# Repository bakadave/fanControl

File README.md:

# fanControl readme

## EEPROM memory map

| memory location | data type | Description|
| ----------- | ----------- | ----------- |
| 1 | bool | WiFi on |
| 2 | bool | 5V PSU |
| 3 | bool | USB sense |
| 4 | float | cal_a |
| 5 |  | cal_a |
| 6 |  | cal_a |
| 7 |  | cal_a |
| 8 | float | cal_b |
| 9 |  | cal_b |
| 10 | | cal_b |
| 11 | | cal_b |
| 12 | char[16] | hostname |
| 13 | | hostname |
| 14 | | hostname |
| 15 | | hostname |
| 16 | | hostname |
| 17 | | hostname |
| 18 | | hostname |
| 19 | | hostname |
| 20 | | hostname |
| 21 | | hostname |
| 22 | | hostname |
| 23 | | hostname |
| 24 | | hostname |
| 25 | | hostname |
| 26 | | hostname |
| 27 | | hostname |
| 28 | N/A | unused |
| 29 | N/A | unused |
| 30 | N/A | unused |
| 31 | N/A | unused |
| 32 | N/A | unused |

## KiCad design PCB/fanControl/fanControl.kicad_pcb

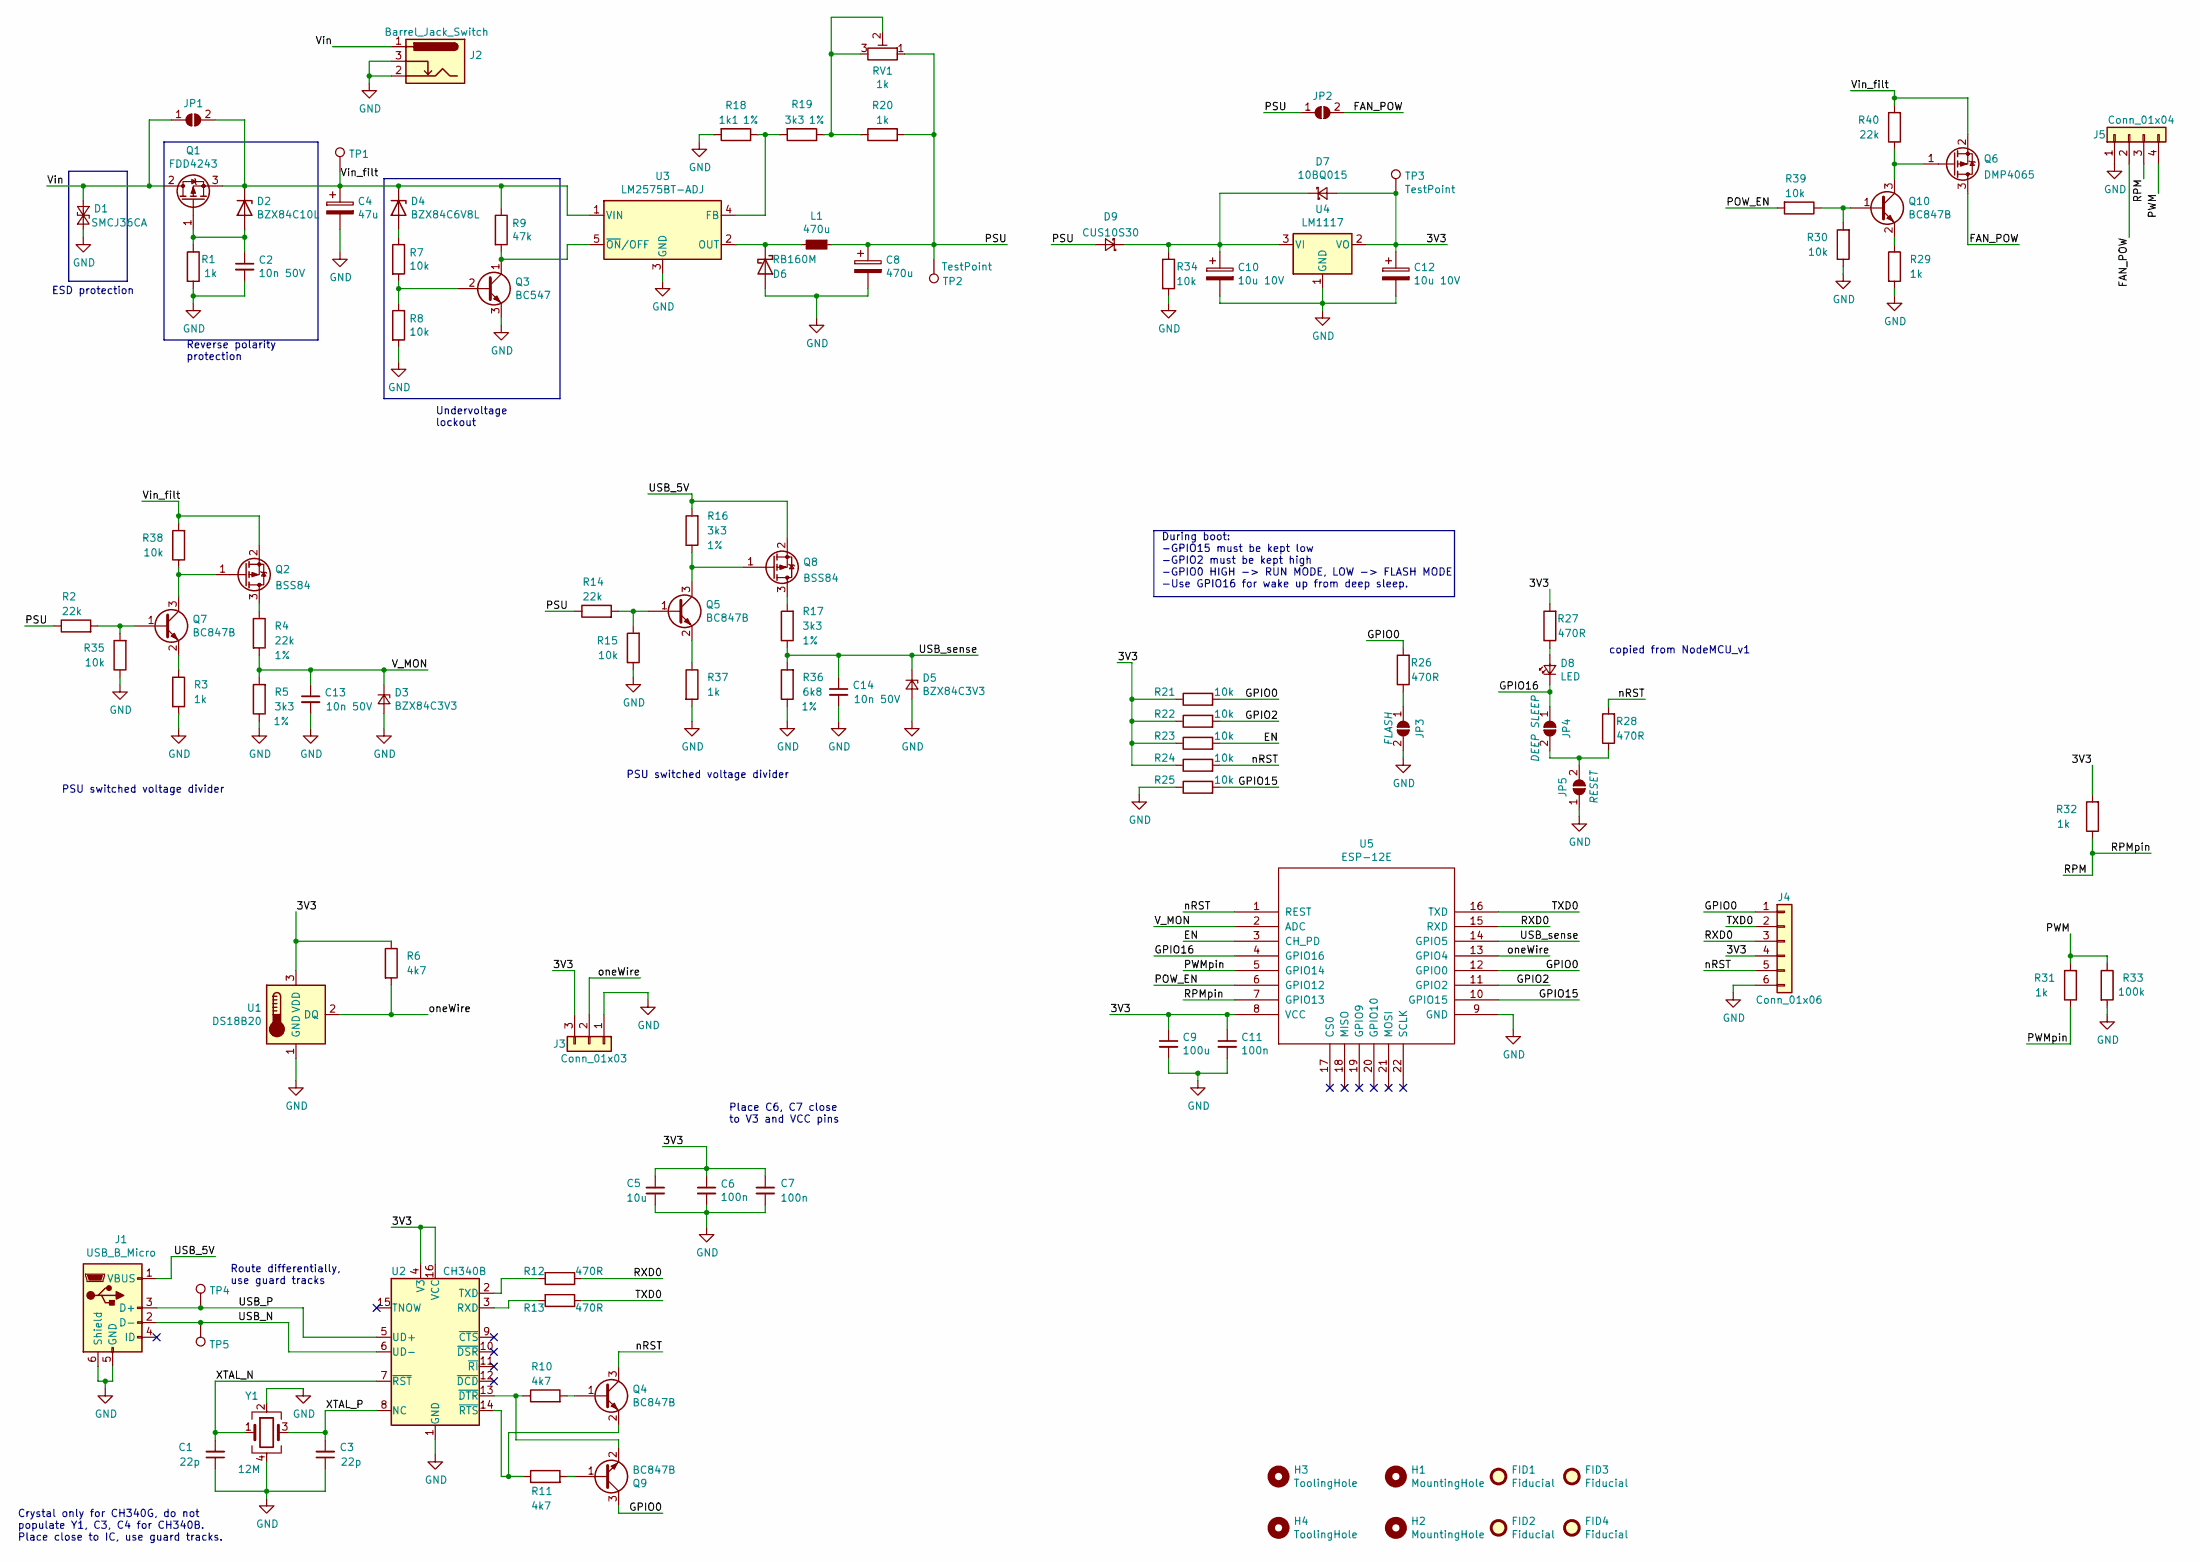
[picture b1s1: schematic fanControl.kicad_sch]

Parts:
C1, C3: 22p; CAP_0805; MPN CC0805FRNPO9BN220; LCSC C541515
C2, C13, C14: 10n 50V; CAP_0805; MPN CC0805JKNPO9BN103; LCSC C527201
C4: 47u; C_Radial_D6.3mm_H11.0mm_P2.50mm
C5: 10u; CAP_0805; MPN CC0805ZKY5V6BB106; LCSC C88484
C6, C7, C11: 100n; CAP_0805; MPN CC0805KRX7R9BB104; LCSC C49678
C8: 470u; C_Radial_D8.0mm_H11.5mm_P3.50mm
C9: 100u; C_1206_3216Metric; MPN CC1206MKX5R5BB107; LCSC C110048
C10, C12: 10u 10V; CP_EIA-3216-18_Kemet-A_Pad1.58x1.35mm_HandSolder; MPN T529P106M010AAE200; LCSC C696821
D1: SMCJ36CA; D_SMC; MPN SMCJ36CA; LCSC C2831485
D2: BZX84C10L; D_SOT-23_ANK; MPN BZX84C10LT1G; LCSC C82476
D3, D5: BZX84C3V3; D_SOT-23_ANK; MPN BZX84C3V3LT1G; LCSC C82473
D4: BZX84C6V8L; D_SOT-23_ANK; MPN BZX84C6V8LT1G; LCSC C90848
D6: RB160M; D_SOD-123; MPN RB160M-40TR; LCSC C123003
D7: 10BQ015; D_SMB; MPN VS-10BQ015-M3/5BT; LCSC C413466
D8: LED; LED_0805; MPN 17-215/BHC-AP1Q2/3T; LCSC C131208
D9: CUS10S30; D_SOD-323_HandSoldering; MPN CUS10S30,H3F; LCSC C146335
FID1, FID2, FID3, FID4: Fiducial; Fiducial_0.5mm_Mask1.5mm
H1, H2: MountingHole; MountingHole_3.2mm_M3
H3, H4: ToolingHole; JLC_toolinghole
J1: USB_B_Micro; USB_Micro-B_Molex-105017-0001; MPN 1050170001; LCSC C136000
J2: Barrel_Jack_Switch; BarrelJack_GCT_DCJ200-10-A_Horizontal; MPN 694106301002
J3: Conn_01x03; Molex_KK-254_AE-6410-03A_1x03_P2.54mm_Vertical
J4: Conn_01x06; PinHeader_1x06_P2.54mm_Vertical
J5: Conn_01x04; Molex_KK-254_AE-6410-04A_1x04_P2.54mm_Vertical
JP1, JP2, JP3, JP4, JP5: SolderJumper_2_Open; SolderJumper-2_P1.3mm_Open_TrianglePad1.0x1.5mm
L1: 470u; L_Radial_D10.5mm_P5.00mm_Abacron_AISR-01
Q1: FDD4243; TO-252-2; MPN FDD4243; LCSC C709958
Q2, Q8: BSS84; SOT-23; MPN BSS84PH6327; LCSC C152212
Q3: BC547; TO-92_Inline_Wide; MPN BC547B; LCSC C713613
Q4, Q5, Q7, Q9, Q10: BC847B; SOT-23; MPN BC847BLT1G; LCSC C94393
Q6: DMP4065; SOT-23; MPN DMP4065S-7; LCSC C182476
R1, R3, R20, R29, R31, R32, R37: 1k; RES_0805; MPN RC0805JR-071KL; LCSC C100046
R2, R4, R14, R40: 22k; RES_0805; MPN RC0805FR-0722KL; LCSC C114565
R5, R16, R17, R19: 3k3; RES_0805; MPN RC0805FR-073K3L; LCSC C114531
R6, R10, R11: 4k7; RES_0805; MPN RC0805FR-074K7L; LCSC C60816
R7, R8, R15, R21, R22, R23, R24, R25, R30, R34, R35, R38, R39: 10k; RES_0805; MPN RC0805JR-0710KL; LCSC C100047
R9: 47k; RES_0805; MPN RC0805JR-0747KL; LCSC C131051
R12, R13, R26, R27, R28: 470R; RES_0805; MPN RC0805JR-07470RL; LCSC C114747
R18: 1k1; RES_0805; MPN RC0805FR-071K1L; LCSC C185294
R33: 100k; RES_0805; MPN RC0805JR-07100KL; LCSC C100049
R36: 6k8; RES_0805; MPN RC0805FR-076K8L; LCSC C114550
RV1: 1k; pot; MPN VG039NCHXTB102; LCSC C128543
TP1, TP2, TP3, TP4, TP5: TestPoint; TestPoint_Pad_D1.0mm
U1: DS18B20; TO-92_Inline_Wide; MPN DS18B20+; LCSC C9753
U2: CH340B; SOIC-16_3.9x9.9mm_P1.27mm; MPN CH340B; LCSC C81010
U3: LM2575BT-ADJ; TO-220-5_Vertical; MPN LM2575T-ADJ; LCSC C434579
U4: LM1117; SOT-223-3_TabPin2; MPN LM1117IMPX-3.3/NOPB; LCSC C23984
U5: ESP-12E; MPN ESP-12E; LCSC C89297
Y1: 12M; Crystal_SMD_3225-4Pin_3.2x2.5mm; MPN S3212000101080; LCSC C390763

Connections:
/3V3: C5.1, C6.1, C7.1, C9.1, C11.1, C12.1, D7.2 (A), J3.3, J4.4, R6.1, R21.1, R22.1, R23.1, R24.1, R27.2, R32.2, TP3.1, U1.3 (VDD), U2.4 (V3), U2.16 (VCC), U4.2 (VO), U5.8 (VCC)
/EN: R23.2, U5.3 (CH_PD)
/FAN_POW: J5.2, JP2.2 (B), Q6.3 (D)
/GPIO0: J4.1, Q9.3 (C), R21.2, R26.2, U5.12 (GPIO0)
/GPIO2: R22.2, U5.11 (GPIO2)
/GPIO15: R25.2, U5.10 (GPIO15)
/GPIO16: D8.1 (K), JP4.1 (A), U5.4 (GPIO16)
/POW_EN: R39.2, U5.6 (GPIO12)
/PSU: C8.1, D9.2 (A), JP2.1 (A), L1.1, R2.1, R14.1, R20.2, RV1.1, TP2.1
/PWM: J5.4, R31.2, R33.1
/PWMpin: R31.1, U5.5 (GPIO14)
/RPM: J5.3, R32.1, U5.7 (GPIO13)
/RXD0: J4.3, R12.1, U5.15 (RXD)
/TXD0: J4.2, R13.1, U5.16 (TXD)
/USB_5V: J1.1 (VBUS), Q8.2 (S), R16.2
/USB_N: J1.2 (D-), TP5.1, U2.6 (UD-)
/USB_P: J1.3 (D+), TP4.1, U2.5 (UD+)
/USB_sense: C14.1, D5.1 (K), R17.1, R36.2, U5.14 (GPIO5)
/V_MON: C13.1, D3.1 (K), R4.2, R5.2, U5.2 (ADC)
/Vin: D1.1 (K), J2.1, JP1.1 (A), Q1.2 (D)
/Vin_filt: C4.1, D2.1 (K), D4.1 (K), JP1.2 (B), Q1.3 (S), Q2.2 (S), Q6.2 (S), R9.1, R38.2, R40.2, TP1.1, U3.1 (VIN)
/XTAL_N: C1.2, U2.7 (~RST), Y1.1
/XTAL_P: C3.2, U2.8 (NC), Y1.3
/nRST: J4.5, Q4.3 (C), R24.2, R28.2, U5.1 (REST)
/oneWire: J3.2, R6.2, U1.2 (DQ), U5.13 (GPIO4)
GND: C1.1, C2.2, C3.1, C4.2, C5.2, C6.2, C7.2, C8.2, C9.2, C10.2, C11.2, C12.2, C13.2, C14.2, D1.2 (A), D3.2 (A), D5.2 (A), D6.2 (A), J1.5 (GND), J1.6 (Shield), J2.2, J2.3, J3.1, J4.6, J5.1, JP3.2 (B), JP5.1 (A), Q3.3 (E), R1.2, R3.2, R5.1, R8.2, R15.1, R18.2, R25.1, R29.2, R30.1, R33.2, R34.2, R35.1, R36.1, R37.2, U1.1 (GND), U2.1 (GND), U3.3 (GND), U4.1 (GND), U5.9 (GND), Y1.2, Y1.4
unnamed: C2.1, D2.2 (A), Q1.1 (G), R1.1
unnamed: C10.1, D7.1 (K), D9.1 (K), R34.1, U4.3 (VI)
unnamed: D4.2 (A), R7.1
unnamed: D6.1 (K), L1.2, U3.2 (OUT)
unnamed: D8.2 (A), R27.1
unnamed: JP3.1 (A), R26.1
unnamed: JP4.2 (B), JP5.2 (B), R28.1
unnamed: Q2.1 (G), Q7.3 (C), R38.1
unnamed: Q2.3 (D), R4.1
unnamed: Q3.1 (C), R9.2, U3.5 (~ON/OFF)
unnamed: Q3.2 (B), R7.2, R8.1
unnamed: Q4.1 (B), R10.2
unnamed: Q4.2 (E), R11.1, U2.14 (~RTS)
unnamed: Q5.3 (C), Q8.1 (G), R16.1
unnamed: Q6.1 (G), Q10.3 (C), R40.1
unnamed: Q7.1 (B), R2.2, R35.2
unnamed: Q7.2 (E), R3.1
unnamed: Q9.1 (B), R11.2
unnamed: Q9.2 (E), R10.1, U2.13 (~DTR)
unnamed: R12.2, U2.2 (TXD)
unnamed: R13.2, U2.3 (RXD)
unnamed: Q5.1 (B), R14.2, R15.2
unnamed: Q8.3 (D), R17.2
unnamed: R18.1, R19.2, U3.4 (FB)
unnamed: R19.1, R20.1, RV1.2, RV1.3
unnamed: Q10.2 (E), R29.1
unnamed: Q10.1 (B), R30.2, R39.1
unnamed: Q5.2 (E), R37.1

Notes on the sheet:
PSU switched voltage divider
ESD protection
Undervoltage lockout
Place C6, C7 close to V3 and VCC pins
Route differentially, use guard tracks
copied from NodeMCU_v1
During boot: -GPIO15 must be kept low -GPIO2 must be kept high -GPIO0 HIGH -> RUN MODE, LOW -> FLASH MODE -Use GPIO16 for wake up from deep sleep.
Crystal only for CH340G, do not populate Y1, C3, C4 for CH340B. Place close to IC, use guard tracks.
Reverse polarity protection

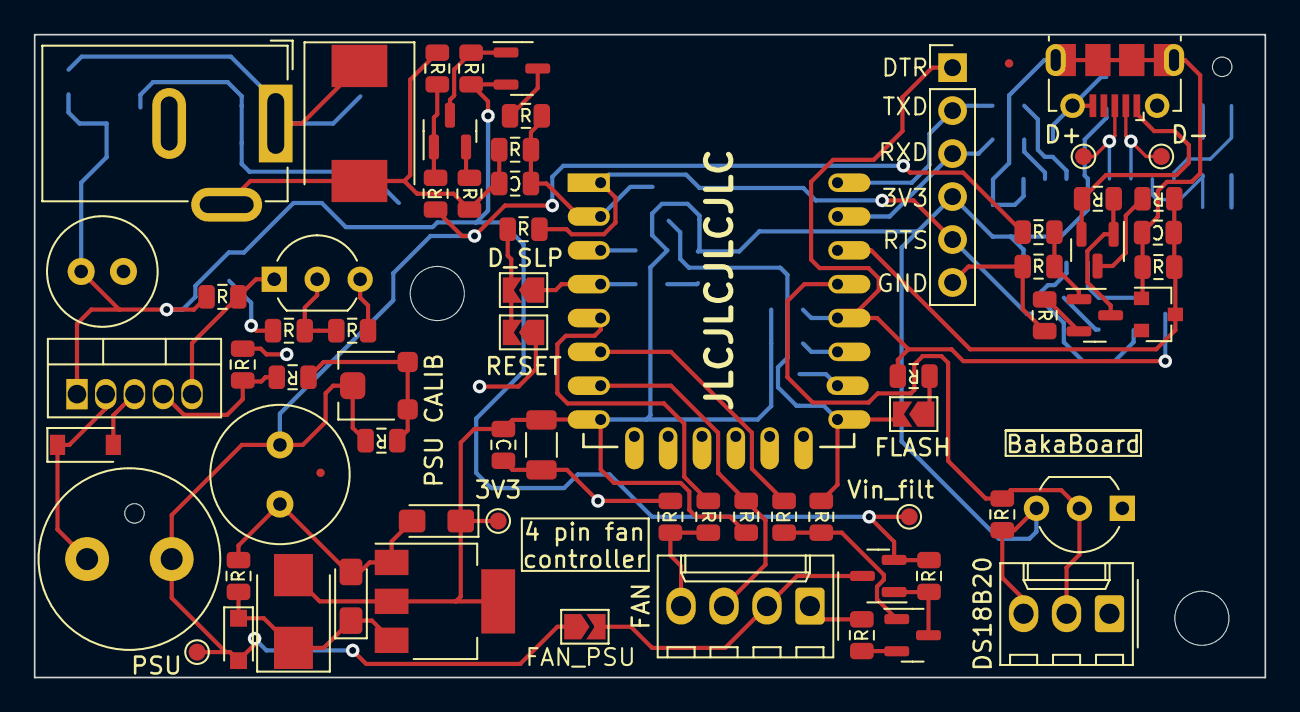
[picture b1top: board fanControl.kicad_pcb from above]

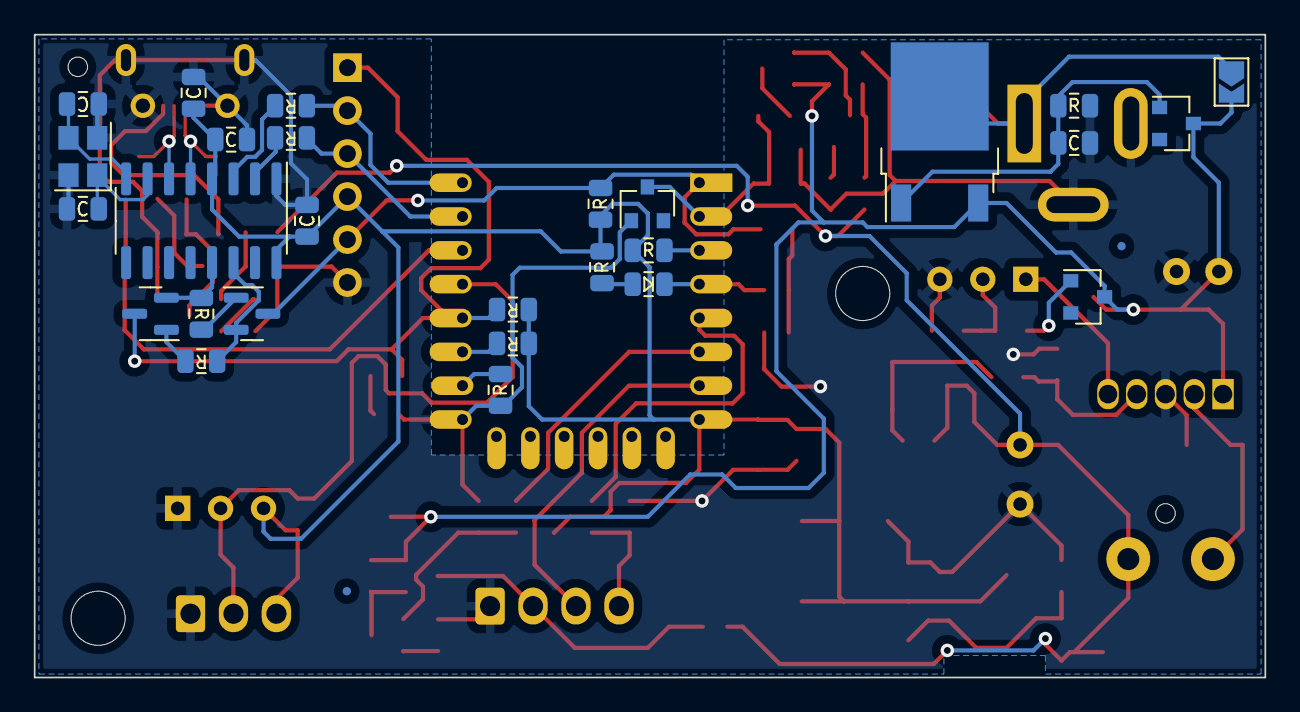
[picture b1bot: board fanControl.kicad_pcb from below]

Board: 2 copper layers, 72.8 x 38.0 mm, 104 parts (29 on the bottom side), 54 nets.

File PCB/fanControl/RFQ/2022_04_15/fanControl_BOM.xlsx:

Reference | Quantity | Value | Footprint | Datasheet | LCSC | MPN | Manufacturer | Supplier | URL | RMK
C1 C3 | 2 | 22p | agro-footprint:CAP_0805 | https://datasheet.lcsc.com/lcsc/2006151142_YAGEO-CC0805FRNPO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 | C541515 | CC0805FRNPO9BN220 | Yageo | LCSC
C10 C12 | 2 | 10u 10V | Capacitor_Tantalum_SMD:CP_EIA-3216-18_Kemet-A_Pad1.58x1.35mm_HandSolder | https://datasheet.lcsc.com/lcsc/2011031906_KEMET-T529P106M01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 | C696821 | T529P106M010AAE200 | KEMET | LCSC
C2 C13 C14 | 3 | 10n 50V | agro-footprint:CAP_0805 | https://datasheet.lcsc.com/lcsc/2005262134_YAGEO-CC0805JKNPO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 | C527201 | CC0805JKNPO9BN103 | Yageo | LCSC
C4 | 1 | 47u | Capacitor_THT:C_Radial_D6.3mm_H11.0mm_P2.50mm |  |  |  |  | Ãrwill | https://arwill.hu/termekek/passziv-alkatreszek/kondenzatorok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
C5 | 1 | 10u | agro-footprint:CAP_0805 | https://datasheet.lcsc.com/lcsc/1810311438_YAGEO-CC0805ZKY5V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 | C88484 | CC0805ZKY5V6BB106 | Yageo | LCSC
C6 C7 C11 | 3 | 100n | agro-footprint:CAP_0805 | https://datasheet.lcsc.com/lcsc/1810101813_YAGEO-CC0805KRX7R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 | C49678 | CC0805KRX7R9BB104 | Yageo | LCSC
C8 | 1 | 470u | Capacitor_THT:C_Radial_D8.0mm_H11.5mm_P3.50mm |  |  |  |  | Ãrwill | https://arwill.hu/termekek/passziv-alkatreszek/kondenzatorok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
C9 | 1 | 100u | Capacitor_SMD:C_1206_3216Metric | https://datasheet.lcsc.com/lcsc/2006191032_YAGEO-CC1206MKX5R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 | C110048 | CC1206MKX5R5BB107 | Yageo | LCSC
D1 | 1 | SMCJ36CA | Diode_SMD:D_SMC | https://datasheet.lcsc.com/lcsc/2110190930_BOURNS-SMCJ36CA_C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 | C2831485 | SMCJ36CA | Bourns | LCSC
D2 | 1 | BZX84C10L | Diode_SMD:D_SOT-23_ANK | https://datasheet.lcsc.com/lcsc/1810301517_onsemi-BZX84C10LT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 | C82476 | BZX84C10LT1G | onsemi | LCSC
D3 D5 | 2 | BZX84C3V3 | Diode_SMD:D_SOT-23_ANK | https://datasheet.lcsc.com/lcsc/1810301522_onsemi-BZX84C3V3L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 | C82473 | BZX84C3V3LT1G | onsemi | LCSC
D4 | 1 | BZX84C6V8L | Diode_SMD:D_SOT-23_ANK | https://datasheet.lcsc.com/lcsc/1810301513_onsemi-BZX84C6V8L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 | C90848 | BZX84C6V8LT1G | onsemi | LCSC
D6 | 1 | RB160M | Diode_SMD:D_SOD-123 | https://datasheet.lcsc.com/lcsc/1810131621_ROHM-Semicon-RB16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 | C123003 | RB160M-40TR | Rohm Semiconductor | LCSC
D7 | 1 | 10BQ015 | Diode_SMD:D_SMB | https://datasheet.lcsc.com/lcsc/2001101209_Vishay-Intertech-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 | C413466 | VS-10BQ015-M3/5BT | Vishay | LCSC
D8 | 1 | LED | agro-footprint:LED_0805 | https://datasheet.lcsc.com/lcsc/1811131731_Everlight-Elec-17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 | C131208 | 17-215/BHC-AP1Q2/3T | Everlight Elec | LCSC
D9 | 1 | CUS10S30 | Diode_SMD:D_SOD-323_HandSoldering | https://datasheet.lcsc.com/lcsc/1810181811_TOSHIBA-CUS10S30-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 | C146335 | CUS10S30,H3F | Toshiba | LCSC
J1 | 1 | USB_B_Micro | Connector_USB:USB_Micro-B_Molex-105017-0001 | https://datasheet.lcsc.com/lcsc/1811131824_MOLEX-1050170001_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 | C136000 | 1050170001 | Molex | LCSC
J2 | 1 | Barrel_Jack_Switch | Connector_BarrelJack:BarrelJack_GCT_DCJ200-10-A_Horizontal | https://www.we-online.com/katalog/datasheet/694106301002.pdf |  | 694106301002 | Wuerth | Ãrwill | https://arwill.hu/termekek/csatlakozok/tap/dc/dc-tap-aljzat-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
L1 | 1 | 470u | Inductor_THT:L_Radial_D10.5mm_P5.00mm_Abacron_AISR-01 |  |  |  |  | Ãrwill | https://arwill.hu/termekek/passziv-alkatreszek/induktivitaso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
Q1 | 1 | FDD4243 | Package_TO_SOT_SMD:TO-252-2 | https://datasheet.lcsc.com/lcsc/2007231308_VBsemi-Elec-FDD42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 | C709958 | FDD4243 | VBsemi Elec | LCSC
Q2 Q8 | 2 | BSS84 | Package_TO_SOT_SMD:SOT-23 | https://datasheet.lcsc.com/lcsc/1808281643_Infineon-Technolo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 | C152212 | BSS84PH6327 | Infineon | LCSC
Q4 Q5 Q7 Q9 Q10 | 5 | BC847B | Package_TO_SOT_SMD:SOT-23 | https://datasheet.lcsc.com/lcsc/1810301520_onsemi-BC847BLT1G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 | C94393 | BC847BLT1G | onsemi | LCSC
Q6 | 1 | DMP4065 | Package_TO_SOT_SMD:SOT-23 | https://datasheet.lcsc.com/lcsc/1912111437_Diodes-Incorporat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 | C182476 | DMP4065S-7 | Diodes Incorporated | LCSC
R1 R3 R20 R29 R31 R32 R37 | 7 | 1k | agro-footprint:RES_0805 | https://datasheet.lcsc.com/lcsc/1810010217_YAGEO-RC0805JR-07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 | C100046 | RC0805JR-071KL | Yageo | LCSC
R12 R13 R26 R27 R28 | 5 | 470R | agro-footprint:RES_0805 | https://datasheet.lcsc.com/lcsc/1810162110_YAGEO-RC0805JR-07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 | C114747 | RC0805JR-07470RL | Yageo | LCSC
R18 | 1 | 1k1 | agro-footprint:RES_0805 | https://datasheet.lcsc.com/lcsc/1810241428_YAGEO-RC0805FR-07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 | C185294 | RC0805FR-071K1L | Yageo | LCSC |  | 0.01
R2 R4 R14 R40 | 4 | 22k | agro-footprint:RES_0805 | https://datasheet.lcsc.com/lcsc/1810311430_YAGEO-RC0805FR-07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 | C114565 | RC0805FR-0722KL | Yageo | LCSC |  | 0.01
R33 | 1 | 100k | agro-footprint:RES_0805 | https://datasheet.lcsc.com/lcsc/1810241513_YAGEO-RC0805JR-07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 | C100049 | RC0805JR-07100KL | Yageo | LCSC
R36 | 1 | 6k8 | agro-footprint:RES_0805 | https://datasheet.lcsc.com/lcsc/1810311431_YAGEO-RC0805FR-07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 | C114550 | RC0805FR-076K8L | Yageo | LCSC |  | 0.01
R5 R16 R17 R19 | 4 | 3k3 | agro-footprint:RES_0805 | https://datasheet.lcsc.com/lcsc/1810311430_YAGEO-RC0805FR-07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 | C114531 | RC0805FR-073K3L | Yageo | LCSC |  | 0.01
R6 R10 R11 | 3 | 4k7 | agro-footprint:RES_0805 | https://datasheet.lcsc.com/lcsc/1810161341_YAGEO-RC0805FR-07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 | C60816 | RC0805FR-074K7L | Yageo | LCSC |  | 0.01
R7 R8 R15 R21 R22 R23 R24 R25 R30 R34 R35 R38 R39 | 13 | 10k | agro-footprint:RES_0805 | https://datasheet.lcsc.com/lcsc/1810171610_YAGEO-RC0805JR-07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 | C100047 | RC0805JR-0710KL | Yageo | LCSC
R9 | 1 | 47k | agro-footprint:RES_0805 | https://datasheet.lcsc.com/lcsc/1810311310_YAGEO-RC0805JR-07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 | C131051 | RC0805JR-0747KL | Yageo | LCSC
RV1 | 1 | 1k | fanControl:pot | https://datasheet.lcsc.com/lcsc/1810170727_HDK-Hokuriku-Elec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 | C128543 | VG039NCHXTB102 | HDK | LCSC
U2 | 1 | CH340B | Package_SO:SOIC-16_3.9x9.9mm_P1.27mm | https://www.mpja.com/download/35227cpdata.pdf | C81010 | CH340B | WCH | LCSC
U3 | 1 | LM2575BT-ADJ | Package_TO_SOT_THT:TO-220-5_Vertical | https://datasheet.lcsc.com/lcsc/1912111437_HGSEMI-LM2575T-AD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 | C434579 | LM2575T-ADJ | HGSEMI | LCSC
U4 | 1 | LM1117 | Package_TO_SOT_SMD:SOT-223-3_TabPin2 | https://datasheet.lcsc.com/lcsc/1809301716_Texas-Instruments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 | C23984 | LM1117IMPX-3.3/NOPB | Texas Instruments | LCSC
U5 | 1 | ESP-12E | ESP8266:ESP-12E | https://components101.com/sites/default/files/2021-09/ESP12E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 | C89297 | ESP-12E | Ai-Thinker | LCSC
Y1 | 1 | 12M | Crystal:Crystal_SMD_3225-4Pin_3.2x2.5mm | https://datasheet.lcsc.com/lcsc/1912111437_JGHC-S32120001010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 | C390763 | S3212000101080 | JGHC | LCSC

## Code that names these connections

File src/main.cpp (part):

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
constexpr uint32_t BAUDRATE = 9600;
constexpr uint32_t PWMfreq = 25000;
constexpr uint8_t rpmPin = 13;      //GPIO13
constexpr uint8_t pwmPin = 14;      //GPIO14
constexpr uint8_t onewireBUS = 4;   //GPIO4
constexpr uint8_t PowEn = 12;       //GPIO12
constexpr uint8_t USBpin = 5;       //GPIO5
constexpr uint8_t Vmon = A0;        //ADC
constexpr uint8_t resolution = 9;
constexpr unsigned long numRegs = 12;
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    pinMode(Vmon, INPUT);
    pinMode(USBpin, INPUT);
    pinMode(PowEn, OUTPUT);
    pinMode(pwmPin, OUTPUT);
    analogWriteFreq(PWMfreq);
    analogWriteResolution(10);  /*! @link https://github.com/esp8266/Arduino/pull/7456 */
    analogWrite(pwmPin, pwm);
    attachInterrupt(digitalPinToInterrupt(rpmPin), rpmISR, CHANGE);
    inputSerialString.reserve(buff_size);

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    pid.Kd = (float)modbus.Hreg(8) / 1000;

    pwm = pid.compute(rpm, deltaT);
    analogWrite(pwmPin, pwm);
    modbus.Hreg(3, pwm);
}

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
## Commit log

2021-08-26 basic functionality
2021-08-26 esp branch w/ new modbus lib & RTU functionality
2021-08-26 added WiFiMulti
2021-08-26 mDNS address passed from platformio.ini
2021-08-26 added port as build_flag
2021-08-26 modbus over TCP/IP
2021-08-27 Serial debug enabled and minor optimisations
2021-08-27 changed Hreg numbering
2021-08-27 fixed compiler warnings
2021-08-30 added PID control
2021-10-22 PID tuning
2021-10-26 PWM set to 10bit
2022-02-05 PCB file added
2022-02-05 KiCad 6 migration
2022-02-06 LCSC BOM done
2022-03-26 ver2
2022-04-12 before optocouplers
2022-04-20 RFQ2
2022-05-06 changed simulations
2022-05-06 added readme
2022-05-07 calculation updates
2022-05-07 EEPROM writer PoC
2022-05-07 full functionality
2022-05-07 minor changes
2022-05-08 optimalisations
2022-05-08 cleanup
2022-05-08 folder restructure
2022-05-08 expanded EEPROM struct
2022-05-09 backup
2022-05-09 EEPROM setup over serial PoC
2022-05-11 EEPROM functionality
2022-05-11 added PCB backup folder
